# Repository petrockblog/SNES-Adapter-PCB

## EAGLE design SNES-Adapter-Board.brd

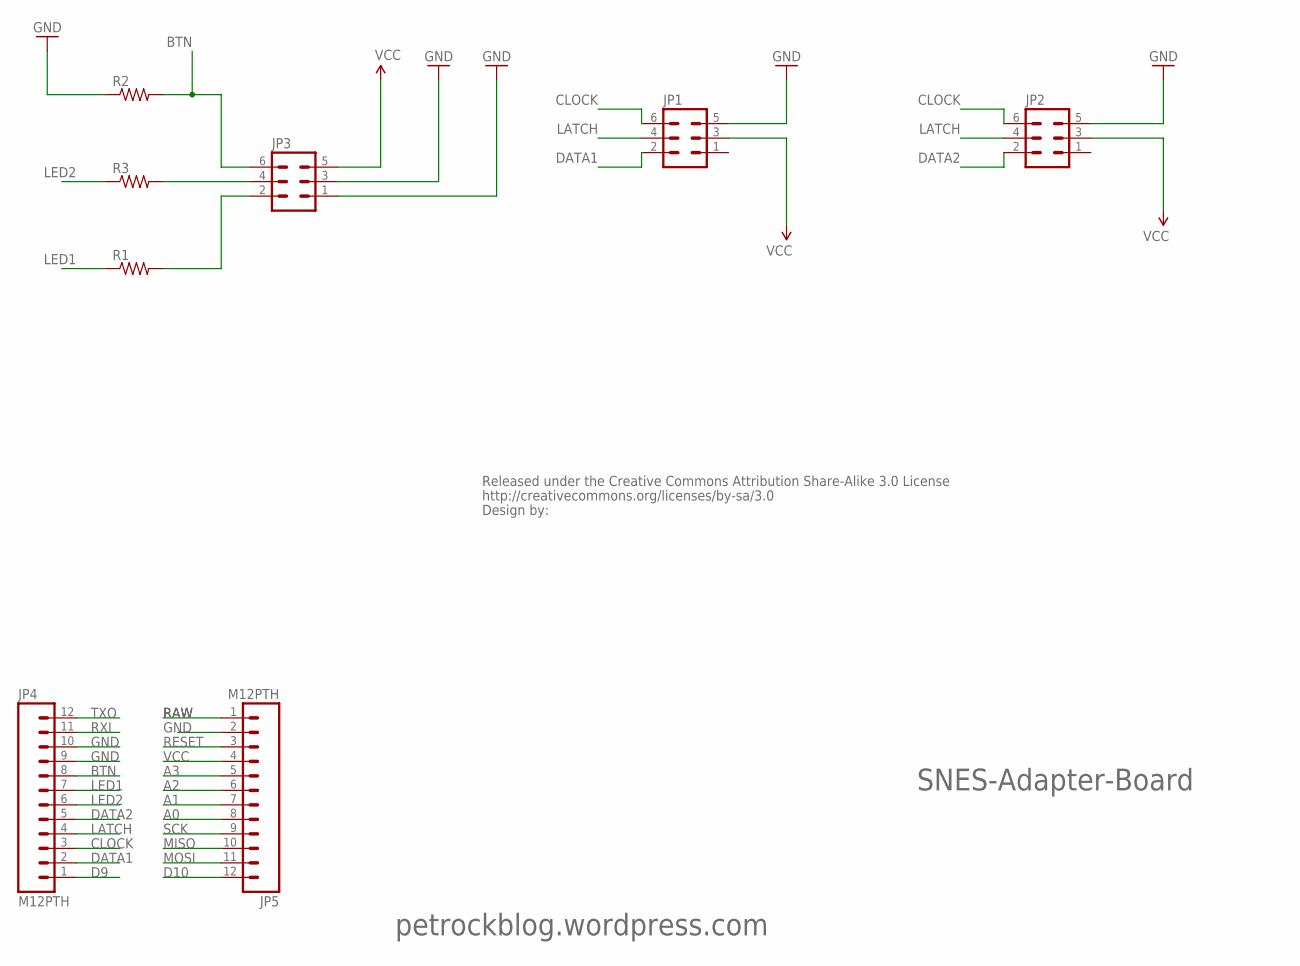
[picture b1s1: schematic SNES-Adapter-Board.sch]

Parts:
JP1, JP2, JP3: ML6
JP4, JP5: M12PTH; 1X12
R1, R2, R3: RESISTORPTH-1/4W; AXIAL-0.4
U$2: CREATIVE_COMMONS

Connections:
A0: JP5.8
A1: JP5.7
A2: JP5.6
A3: JP5.5
BTN: JP3.6, JP4.8, R2.P$2 (2)
CLOCK: JP1.6, JP2.6, JP4.3
D9: JP4.1
D10: JP5.12
DATA1: JP1.2, JP4.2
DATA2: JP2.2, JP4.5
GND: JP1.5, JP2.5, JP3.1, JP3.3, JP4.9, JP4.10, JP5.2, R2.P$1 (1)
LATCH: JP1.4, JP2.4, JP4.4
LED1: JP4.7, R1.P$1 (1)
LED2: JP4.6, R3.P$1 (1)
MISO: JP5.10
MOSI: JP5.11
unnamed: JP3.2, R1.P$2 (2)
unnamed: JP3.4, R3.P$2 (2)
RAW: JP5.1
RESET: JP5.3
RXI: JP4.11
SCK: JP5.9
TXO: JP4.12
VCC: JP1.3, JP2.3, JP3.5, JP5.4

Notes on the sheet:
petrockblog.wordpress.com
SNES-Adapter-Board

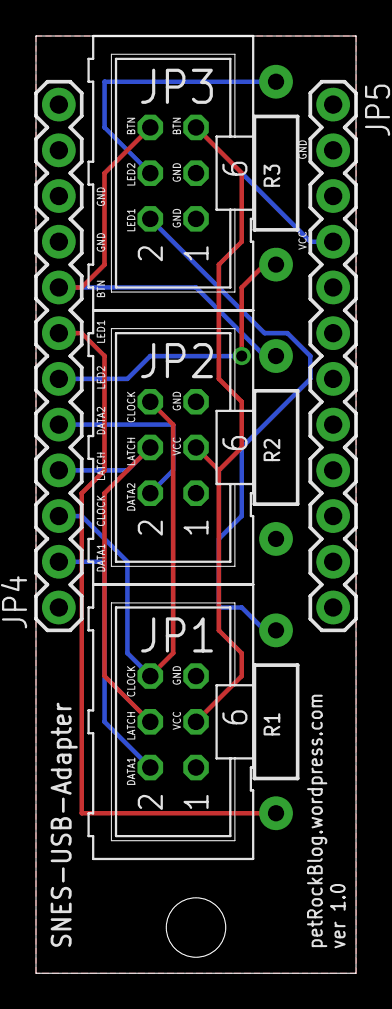
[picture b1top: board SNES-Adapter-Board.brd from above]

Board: 2 copper layers, 17.8 x 52.1 mm, 10 parts (0 on the bottom side), 11 nets.

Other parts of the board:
U$1: STAND-OFF

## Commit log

2012-12-28 First commit.

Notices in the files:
parts and their libraries:
SparkFun: Licensing: CC v3.0 Share-Alike You are welcome to use this library for commercial purposes.
SparkFun-Aesthetics: Released under the Creative Commons Attribution Share-Alike 3.0 License
SparkFun-Aesthetics: http://creativecommons.org/licenses/by-sa/3.0
